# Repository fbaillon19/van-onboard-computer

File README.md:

# 🚐 VOBC - Van Onboard Computer

**V**an **O**nboard **B**oard **C**omputer - Système de monitoring et de gestion pour fourgon aménagé.

## 📋 Présentation

Le VOBC est un ordinateur de bord complet pour fourgon aménagé permettant de :
- 🌡️ Monitorer température intérieure/extérieure et humidité
- ⚡ Gérer l'énergie (batterie, panneaux solaires, consommation)
- ⚠️ Détecter les dangers (CO, fuite de gaz)
- 📊 Mesurer l'horizontalité pour stationnement
- 💧 Surveiller les niveaux d'eau
- 🔔 Alertes sonores et visuelles configurables
- 📈 Historique des données sur carte SD

## 🎯 Fonctionnalités

### Phase 1 - INDISPENSABLE ✅
- [x] Température intérieure + humidité (BME280)
- [x] Température extérieure (DS18B20)
- [x] Détection CO (MQ-7)
- [x] Détection gaz GPL (MQ-2)
- [x] Monitoring batterie (INA226)
- [x] Horizontalité 3 axes (MPU6050)
- [x] Détection ouverture portes (Reed Switch)
- [x] Alertes visuelles (LED RGB) et sonores (Buzzer)
- [x] Affichage LCD 20x4 I2C
- [x] Navigation par encodeur rotatif

### Phase 2 - IMPORTANTE 🔶
- [ ] Niveaux réservoirs eau (HC-SR04)
- [ ] Ventilation automatique (Module relais)
- [ ] Détecteur de mouvement (PIR)
- [ ] Monitoring panneaux solaires (INA226 #2)
- [ ] Éclairage automatique (LDR)

### Phase 3 - MOYENNE 🔹
- [ ] Horodatage (RTC DS3231)
- [ ] Historique données (Module SD)
- [ ] Orientation/boussole (HMC5883L)
- [ ] Prévision solaire algorithmique
- [ ] Interface Web/Bluetooth (optionnel)

## 🔧 Matériel

### Contrôleur
- Arduino MEGA 2560 R3

### Capteurs Phase 1
- BME280 (I2C) - Température + Humidité + Pression
- INA226 (I2C) - Courant/Tension batterie
- MPU6050 (I2C) - Gyroscope + Accéléromètre
- MQ-7 (Analogique) - Détecteur CO
- MQ-2 (Analogique) - Détecteur GPL/Butane
- DS18B20 (One-Wire) - Température extérieure étanche
- Reed Switch - Détection portes

### Interface
- LCD 20x4 avec module I2C
- Encodeur rotatif KY-040
- LED RGB + Buzzer piézo

### Alimentation
- Convertisseur DC-DC 12V → 5V (LM2596/MP1584) 3A min

Voir [HARDWARE.md](docs/HARDWARE.md) pour détails complets.

## 📁 Structure du projet

```
.
├── README.md                    # Ce fichier
├── LICENSE                      # Licence MIT
├── CHANGELOG.md                 # Historique des versions
├── docs/                        # Documentation
│   ├── HARDWARE.md             # Schémas et câblage
│   ├── SOFTWARE.md             # Architecture logicielle
│   ├── CONFIGURATION.md        # Configuration système
│   ├── INSTALL.md              # Guide d'installation
│   └── images/                 # Schémas et photos
├── firmware/                    # Code Arduino
│   └── van_onboard_computer/
│       ├── van_onboard_computer.ino  # Fichier principal
│       ├── config.h                   # Configuration
│       └── *.cpp/*.h                  # Modules
├── hardware/                    # Fichiers matériels
│   ├── schematics/             # Schémas électriques
│   ├── pcb/                    # PCB (phase finale)
│   └── datasheets/             # Datasheets composants
├── testing/                     # Tests unitaires
│   ├── test_codes/             # Codes de test capteurs
│   └── testing_README.md       # Guide de test
└── tools/                       # Outils et scripts
    └── scripts/                # Scripts utilitaires
```

## 🚀 Installation rapide

### Prérequis
- Arduino IDE 2.x
- Librairies (voir [INSTALL.md](docs/INSTALL.md))

### Étapes
```bash
# Cloner le repo
git clone https://github.com/[votre-username]/van-onboard-computer.git
cd van-onboard-computer

# Installer les librairies nécessaires
# (voir docs/INSTALL.md)

# Ouvrir le firmware
# Arduino IDE: Ouvrir firmware/van_onboard_computer/van_onboard_computer.ino
# PlatformIO: Ouvrir le dossier dans VS Code

# Configurer dans config.h
# Compiler et uploader sur Arduino MEGA
```

## 📚 Documentation

- [Guide matériel](docs/HARDWARE.md) - Schémas de câblage complets
- [Architecture logicielle](docs/SOFTWARE.md) - Structure du code
- [Configuration](docs/CONFIGURATION.md) - Paramétrage système
- [Installation](docs/INSTALL.md) - Guide d'installation pas à pas
- [Tests](testing/testing_README.md) - Procédures de test

## 🧪 Tests

Chaque capteur dispose de son code de test unitaire dans `testing/test_codes/`. Voir [testing_README.md](testing/testing_README.md) pour la procédure complète.

## 🤝 Contribution

Les contributions sont bienvenues ! 

1. Fork le projet
2. Créer une branche (`git checkout -b feature/amelioration`)
3. Commit (`git commit -am 'Ajout fonctionnalité'`)
4. Push (`git push origin feature/amelioration`)
5. Créer une Pull Request

## 📝 Changelog

Voir [CHANGELOG.md](CHANGELOG.md) pour l'historique des versions.

## 📄 Licence

Ce projet est sous licence MIT - voir [LICENSE](LICENSE) pour plus de détails.

## 👤 Auteur

**Frédéric BAILLON**
- GitHub: [@fbaillon19](https://github.com/fbaillon19)

## 🙏 Remerciements

- Communauté Arduino
- Fabricants de capteurs (Bosch, Texas Instruments, etc.)
- Tous les contributeurs du projet

## 📸 Galerie

_Photos à venir lors de l'installation..._

---

⭐ Si ce projet vous aide, n'hésitez pas à lui donner une étoile !

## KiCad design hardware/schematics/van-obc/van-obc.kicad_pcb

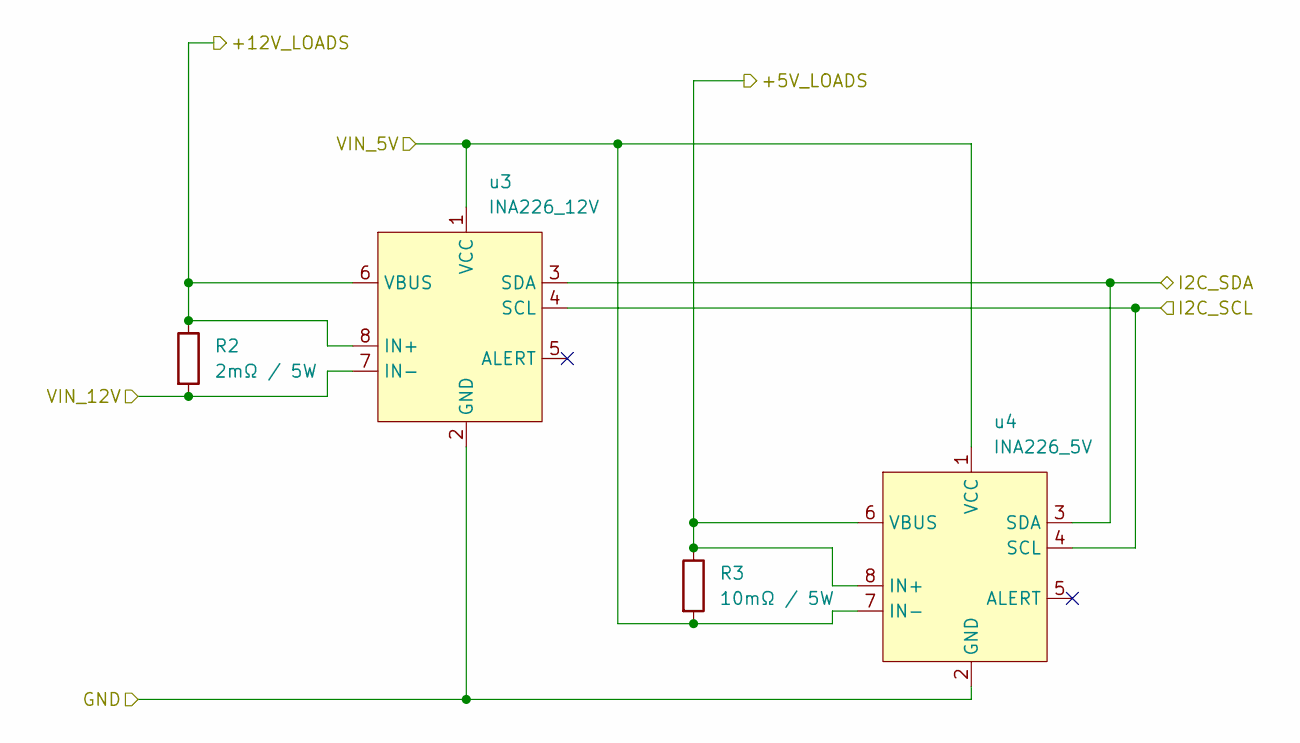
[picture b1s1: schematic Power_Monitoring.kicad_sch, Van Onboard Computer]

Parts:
R2: 2mΩ / 5W; R_2512_6332Metric
R3: 10mΩ / 5W; R_2512_6332Metric
u3: INA226_12V; INA226_Module_Header_1x08
u4: INA226_5V; INA226_Module_Header_1x08

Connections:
/Display_And_UI/+5V: R3.1, u4.6 (VBUS), u4.8 (IN+); also elsewhere on the board
/Display_And_UI/GND: u3.2 (GND), u4.2 (GND); also elsewhere on the board
/Display_And_UI/I2C_SCL: u3.4 (SCL), u4.4 (SCL); also elsewhere on the board
/Display_And_UI/I2C_SDA: u3.3 (SDA), u4.3 (SDA); also elsewhere on the board
/Power_Input/+5V_PROT: R3.2, u3.1 (VCC), u4.1 (VCC), u4.7 (IN-); also elsewhere on the board
/Power_Input/+12V: R2.1, u3.6 (VBUS), u3.8 (IN+); also elsewhere on the board
/Power_Input/+12V_PROT: R2.2, u3.7 (IN-); also elsewhere on the board

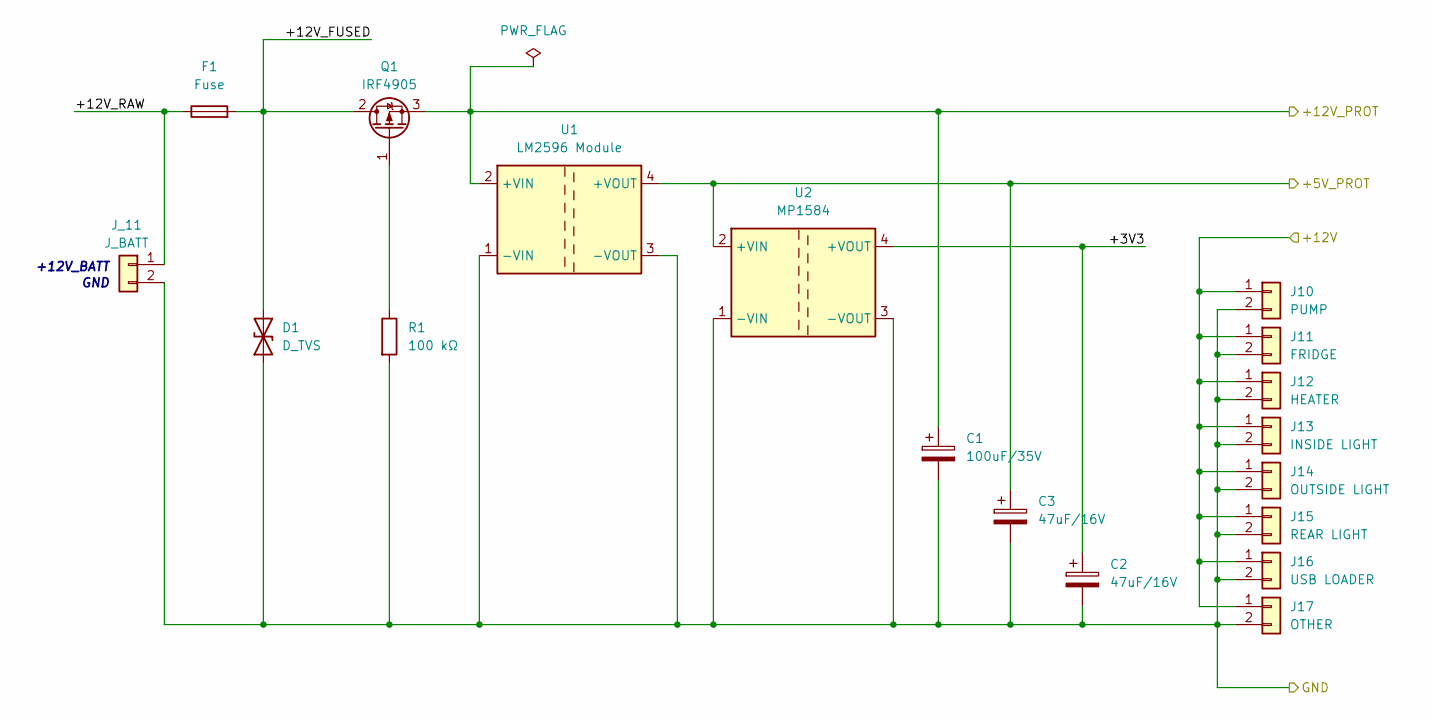
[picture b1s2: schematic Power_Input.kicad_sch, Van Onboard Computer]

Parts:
C1: 100uF/35V; CP_Radial_D8.0mm_P3.50mm
C2, C3: 47uF/16V; CP_Radial_D6.3mm_P2.50mm
D1: D_TVS; D_SMA-SMB_Universal_Handsoldering
F1: Fuse; Fuseholder_Clip-5x20mm_Bel_FC-203-22_Lateral_P17.80x5.00mm_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
J10: PUMP; Connecteur 2 vis
J11: FRIDGE; Connecteur 2 vis
J12: HEATER; Connecteur 2 vis
J13: INSIDE LIGHT; Connecteur 2 vis
J14: OUTSIDE LIGHT; Connecteur 2 vis
J15: REAR LIGHT; Connecteur 2 vis
J16: USB LOADER; Connecteur 2 vis
J17: OTHER; Connecteur 2 vis
J_11: J_BATT; Connecteur 2 vis
Q1: IRF4905; TO-220-3_Vertical
R1: 100 kΩ; R_Axial_DIN0207_L6.3mm_D2.5mm_P10.16mm_Horizontal
U1: LM2596 Module; LM2596_Breakout
U2: MP1584; MP1584_Breakout

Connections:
/Display_And_UI/GND: C1.2, C2.2, C3.2, D1.1 (A1), J10.2, J11.2, J12.2, J13.2, J14.2, J15.2, J16.2, J17.2, J_11.2, R1.2, U1.1 (-VIN), U1.3 (-VOUT), U2.1 (-VIN), U2.3 (-VOUT); also elsewhere on the board
/Power_Input/+3V3: C2.1, U2.4 (+VOUT)
/Power_Input/+5V_PROT: C3.1, U1.4 (+VOUT), U2.2 (+VIN); also elsewhere on the board
/Power_Input/+12V: J10.1, J11.1, J12.1, J13.1, J14.1, J15.1, J16.1, J17.1; also elsewhere on the board
/Power_Input/+12V_FUSED: D1.2 (A2), F1.2, Q1.2 (D)
/Power_Input/+12V_PROT: C1.1, Q1.3 (S), U1.2 (+VIN); also elsewhere on the board
/Power_Input/+12V_RAW: F1.1, J_11.1
unnamed: Q1.1 (G), R1.1

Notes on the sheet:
+12V_BATT
GND

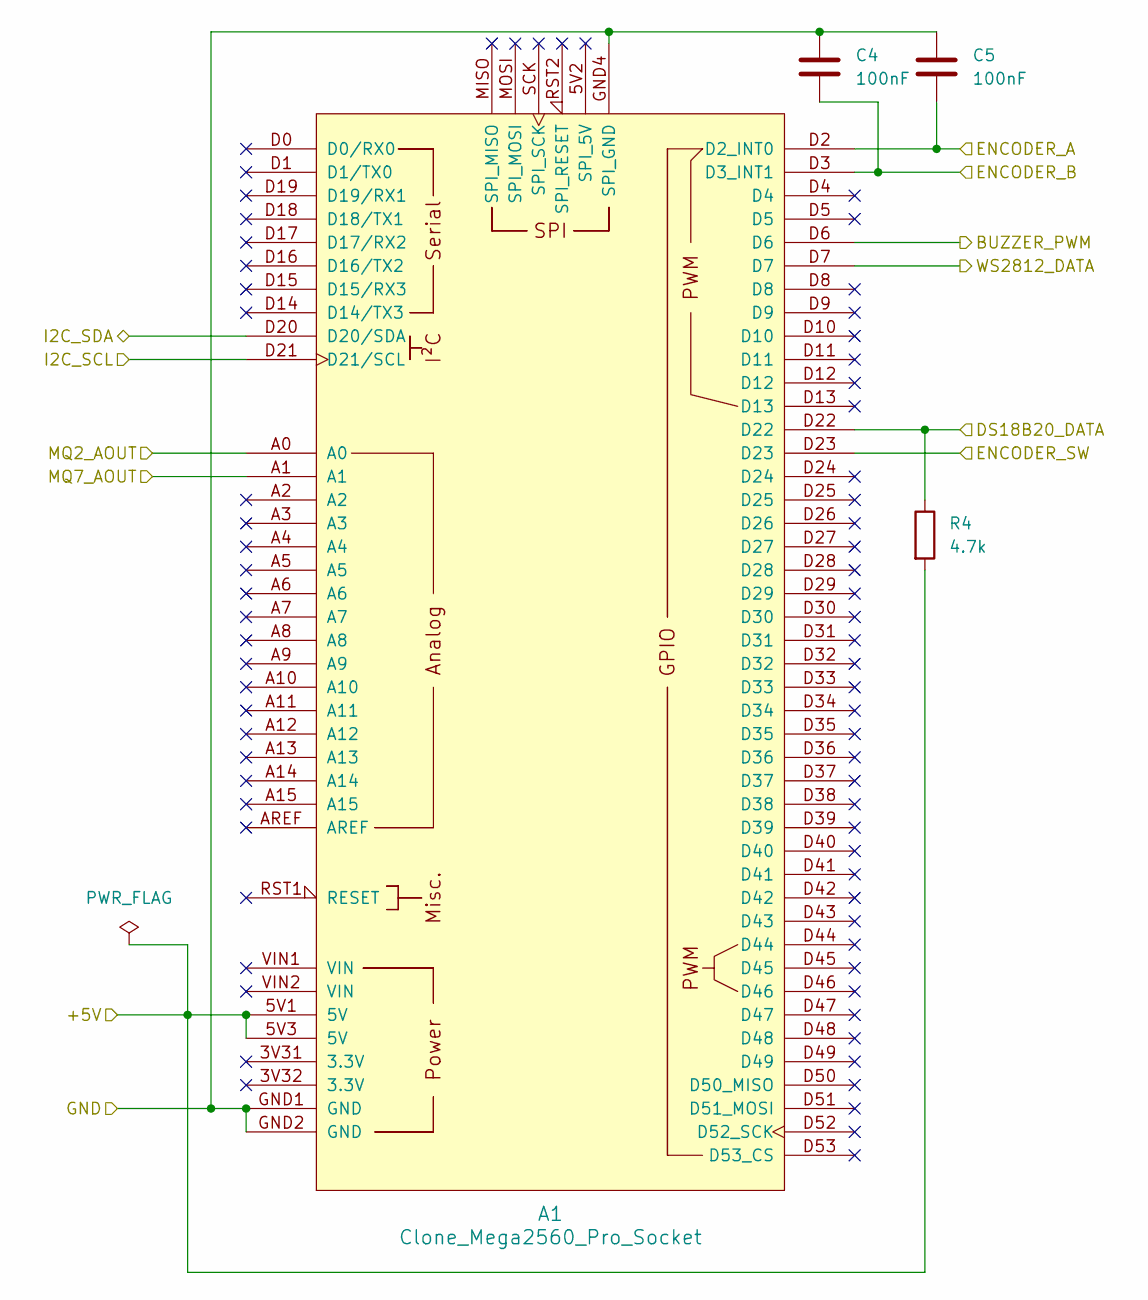
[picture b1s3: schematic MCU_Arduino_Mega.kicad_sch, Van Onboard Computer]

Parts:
A1: Clone_Mega2560_Pro_Socket
C4, C5: 100nF; C_Disc_D4.3mm_W1.9mm_P5.00mm
R4: 4.7k; R_Axial_DIN0207_L6.3mm_D2.5mm_P10.16mm_Horizontal

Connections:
/Display_And_UI/+5V: A1.5V1 (5V), A1.5V3 (5V), R4.2; also elsewhere on the board
/Display_And_UI/BUZZER_PWM: A1.D6; also elsewhere on the board
/Display_And_UI/ENCODER_A: A1.D2 (D2_INT0), C5.2; also elsewhere on the board
/Display_And_UI/ENCODER_B: A1.D3 (D3_INT1), C4.2; also elsewhere on the board
/Display_And_UI/ENCODER_SW: A1.D23; also elsewhere on the board
/Display_And_UI/GND: A1.GND1 (GND), A1.GND2 (GND), A1.GND4 (SPI_GND), C4.1, C5.1; also elsewhere on the board
/Display_And_UI/I2C_SCL: A1.D21 (D21/SCL); also elsewhere on the board
/Display_And_UI/I2C_SDA: A1.D20 (D20/SDA); also elsewhere on the board
/Display_And_UI/WS2812_DATA: A1.D7; also elsewhere on the board
/MCU_Arduino_Mega/DS18B20_DATA: A1.D22, R4.1; also elsewhere on the board
/MCU_Arduino_Mega/MQ2_AOUT: A1.A0; also elsewhere on the board
/MCU_Arduino_Mega/MQ7_AOUT: A1.A1; also elsewhere on the board

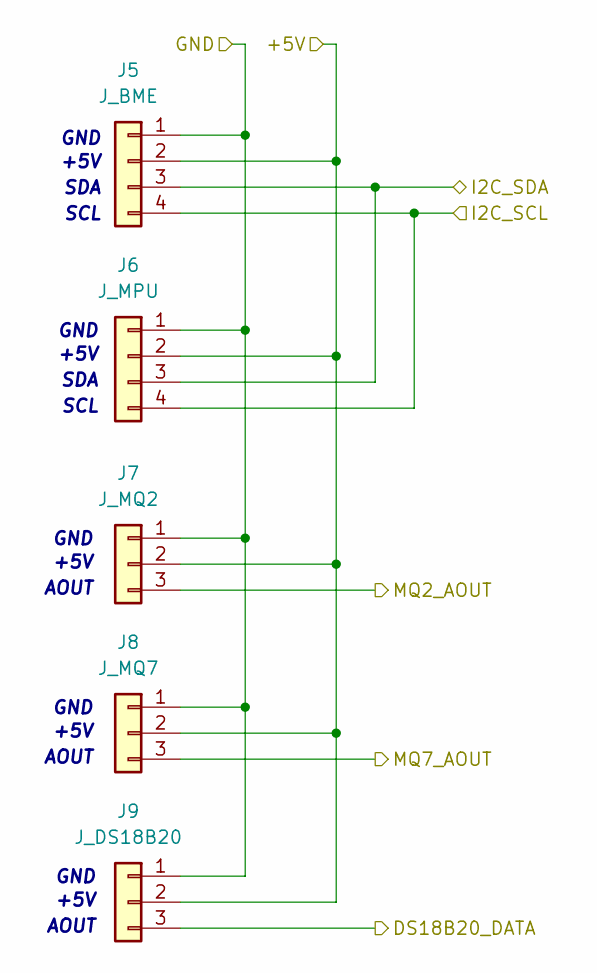
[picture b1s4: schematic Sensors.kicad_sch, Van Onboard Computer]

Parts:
J5: J_BME; PinHeader_1x04_P2.54mm_Vertical
J6: J_MPU; PinHeader_1x04_P2.54mm_Vertical
J7: J_MQ2; PinHeader_1x03_P2.54mm_Vertical
J8: J_MQ7; PinHeader_1x03_P2.54mm_Vertical
J9: J_DS18B20; PinHeader_1x03_P2.54mm_Vertical

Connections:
/Display_And_UI/+5V: J5.2, J6.2, J7.2, J8.2, J9.2; also elsewhere on the board
/Display_And_UI/GND: J5.1, J6.1, J7.1, J8.1, J9.1; also elsewhere on the board
/Display_And_UI/I2C_SCL: J5.4, J6.4; also elsewhere on the board
/Display_And_UI/I2C_SDA: J5.3, J6.3; also elsewhere on the board
/MCU_Arduino_Mega/DS18B20_DATA: J9.3; also elsewhere on the board
/MCU_Arduino_Mega/MQ2_AOUT: J7.3; also elsewhere on the board
/MCU_Arduino_Mega/MQ7_AOUT: J8.3; also elsewhere on the board

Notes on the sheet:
+5V
AOUT
GND
SCL
SDA

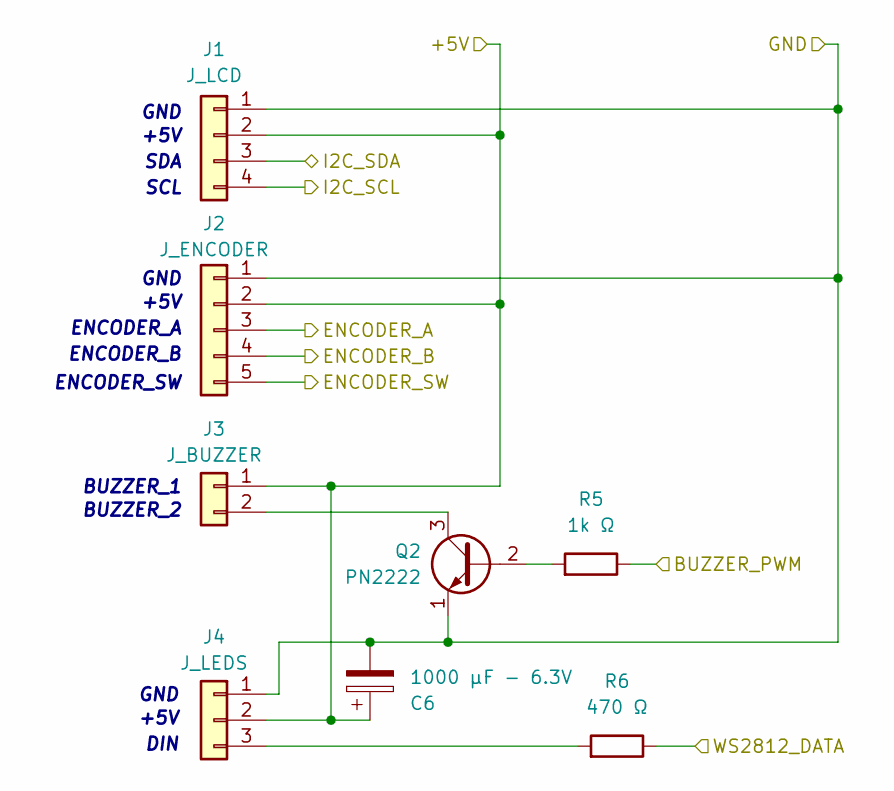
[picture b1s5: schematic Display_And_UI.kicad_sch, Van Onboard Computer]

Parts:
C6: 1000 µF - 6.3V; CP_Radial_D8.0mm_P3.50mm
J1: J_LCD; PinHeader_1x04_P2.54mm_Vertical
J2: J_ENCODER; PinHeader_1x05_P2.54mm_Vertical
J3: J_BUZZER; PinHeader_1x02_P2.54mm_Vertical
J4: J_LEDS; PinHeader_1x03_P2.54mm_Vertical
Q2: PN2222; TO-92_Inline
R5: 1k Ω; R_Axial_DIN0207_L6.3mm_D2.5mm_P10.16mm_Horizontal
R6: 470 Ω; R_Axial_DIN0207_L6.3mm_D2.5mm_P10.16mm_Horizontal

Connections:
/Display_And_UI/+5V: C6.1, J1.2, J2.2, J3.1, J4.2; also elsewhere on the board
/Display_And_UI/BUZZER_PWM: R5.1; also elsewhere on the board
/Display_And_UI/ENCODER_A: J2.3; also elsewhere on the board
/Display_And_UI/ENCODER_B: J2.4; also elsewhere on the board
/Display_And_UI/ENCODER_SW: J2.5; also elsewhere on the board
/Display_And_UI/GND: C6.2, J1.1, J2.1, J4.1, Q2.1 (E); also elsewhere on the board
/Display_And_UI/I2C_SCL: J1.4; also elsewhere on the board
/Display_And_UI/I2C_SDA: J1.3; also elsewhere on the board
/Display_And_UI/WS2812_DATA: R6.1; also elsewhere on the board
unnamed: J3.2, Q2.3 (C)
unnamed: J4.3, R6.2
unnamed: Q2.2 (B), R5.2

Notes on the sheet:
GND
+5V
SDA
ENCODER_A
ENCODER_SW
BUZZER_2
BUZZER_1
SCL
ENCODER_B
DIN

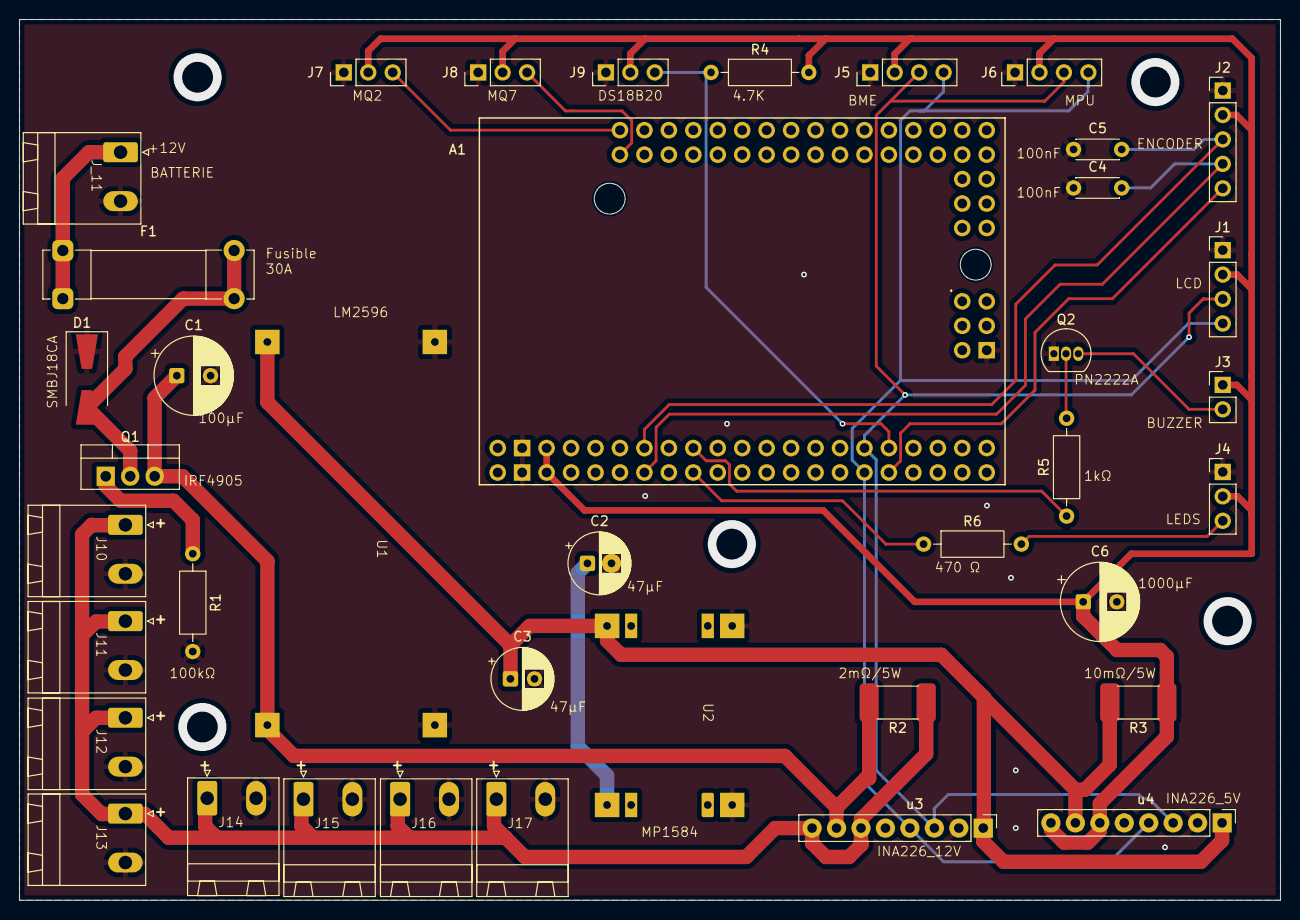
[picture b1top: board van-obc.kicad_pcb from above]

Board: 2 copper layers, 131.0 x 91.5 mm, 39 parts (0 on the bottom side), 22 nets.

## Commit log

2025-11-18 Initial commit: Structure projet VOBC
2025-11-26 feat: Initial implementation v0.1.0 - Core system
    - Add configuration file with all hardware constants and thresholds
    - Add system data structures (modes, screens, alerts, sensors state)
    - Add sensor manager (7 sensors with non-blocking acquisition)
    - Add alert system (hierarchical alerts with buzzer control)
    - Add LED manager (WS2812B 8-LED bar with power/gas/voltage indicators)
    - Add display manager (6 screens with rotary encoder navigation)
2025-11-28 Add KiCad project for Van Onboard Computer schematics
2025-11-30 Add KiCad schematics for Van Onboard Computer (v1.0)
2025-12-10 fix(tests): Corrections majeures KY040, BME280, MPU6050
    - KY040 v2.1.0: Fix comptage + anti-rebond capacitif
    - BME280 v1.0.1: Fix begin() avec &Wire
    - MPU6050 v2.0.0: Simplification (acc only, dérive <2°)
    - Ajout diagnostic_bme280.ino + CHANGELOG
    Tests: 6/11 validés (55%)
2025-12-10 add(test): Ruban LEDs
    - WS2812B v2.0.0: Test matériel et scénarios de mise en oeuvre
    Tests: 7/11 validés (63%)
2025-12-11 add(test): BUZZER
    - BUZZER v1.0.0: Test matériel & fix: préfixe appel fonction tone et notone
    Tests: 8/11 validés (72%)

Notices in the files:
README.md:
License: MIT
